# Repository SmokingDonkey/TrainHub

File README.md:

TrainHub
========

This Repo contains hardware and software parts for a automated model railroad:
- TrainTracker: RFID reader platine for train recognition
- ...

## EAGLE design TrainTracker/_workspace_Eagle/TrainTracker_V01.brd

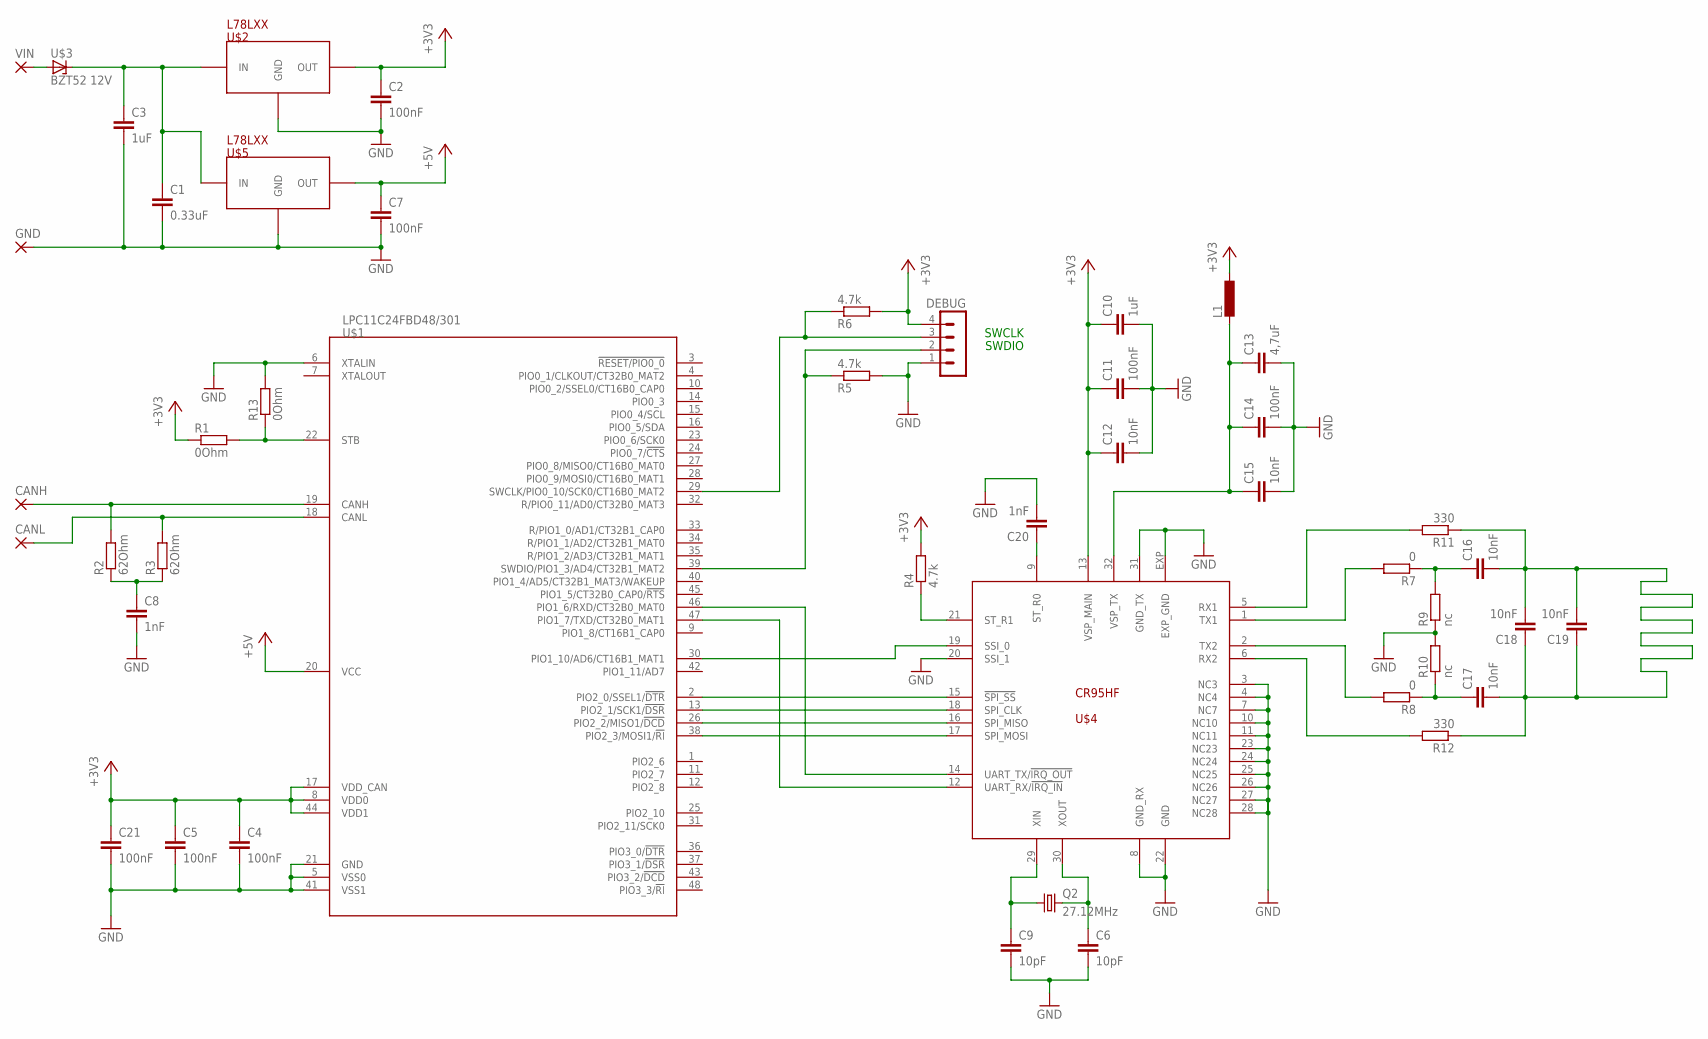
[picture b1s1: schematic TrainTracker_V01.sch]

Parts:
C1: 0.33uF; C0402
C2, C4, C5, C7, C11, C14, C21: 100nF; C0402
C3, C10: 1uF; C0603K
C6, C9: 10pF; C0402
C8, C20: 1nF; C0402
C12, C15, C16, C17, C18, C19: 10nF; C0402
C13: 4,7uF; C0603K
CANH: SMD5; SMD2,54-5,08
CANL: SMD5; SMD2,54-5,08
DEBUG: MA04-1
GND: SMD5; SMD2,54-5,08
L1: L-EUL3216C; L3216C
Q2: 27.12MHz; CTS406
R1, R13: 0Ohm; R0402
R2, R3: 62Ohm; R0402
R4, R5, R6: 4.7k; R0402
R7, R8: 0; R0402
R9, R10: nc; R0402
R11, R12: 330; R0402
U$1: LPC11C24FBD48/301; LQFP48
U$2, U$5: L78LXX; SO8
U$3: BZT52 12V; SOD123
U$4: CR95HF; VFQFPN32
VIN: SMD5; SMD2,54-5,08

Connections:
+3V3: C2.1, C4.1, C5.1, C10.1, C11.1, C12.1, C21.1, DEBUG.4, L1.1, R1.1, R4.2, R6.2, U$1.8 (VDD0), U$1.17 (VDD_CAN), U$1.44 (VDD1), U$2.1 (OUT), U$4.13 (VSP_MAIN)
+5V: C7.1, U$1.20 (VCC), U$5.1 (OUT)
GND: C1.2, C2.2, C3.2, C4.2, C5.2, C6.2, C7.2, C8.2, C9.2, C10.2, C11.2, C12.2, C13.2, C14.2, C15.2, C20.2, C21.2, DEBUG.1, GND.1, R5.2, R9.1, R10.2, R13.2, U$1.5 (VSS0), U$1.6 (XTALIN), U$1.21 (GND), U$1.41 (VSS1), U$2.2 (GND), U$2.3 (GND), U$2.6 (GND), U$2.7 (GND), U$4.3 (NC3), U$4.4 (NC4), U$4.7 (NC7), U$4.8 (GND_RX), U$4.10 (NC10), U$4.11 (NC11), U$4.20 (SSI_1), U$4.22 (GND), U$4.23 (NC23), U$4.24 (NC24), U$4.25 (NC25), U$4.26 (NC26), U$4.27 (NC27), U$4.28 (NC28), U$4.31 (GND_TX), U$4.EXP (EXP_GND), U$5.2 (GND), U$5.3 (GND), U$5.6 (GND), U$5.7 (GND)
unnamed: U$3.1 (A), VIN.1
unnamed: C1.1, C3.1, U$2.8 (IN), U$3.2 (C), U$5.8 (IN)
unnamed: R1.2, R13.1, U$1.22 (STB)
unnamed: C8.1, R2.1, R3.1
unnamed: CANH.1, R2.2, U$1.19 (CANH)
unnamed: CANL.1, R3.2, U$1.18 (CANL)
unnamed: U$1.2 (PIO2_0/SSEL1/!DTR), U$4.15 (!SPI_SS)
unnamed: C20.1, U$4.9 (ST_R0)
unnamed: U$1.13 (PIO2_1/SCK1/!DSR), U$4.18 (SPI_CLK)
unnamed: U$1.26 (PIO2_2/MISO1/!DCD), U$4.16 (SPI_MISO)
unnamed: U$1.38 (PIO2_3/MOSI1/!RI), U$4.17 (SPI_MOSI)
unnamed: R4.1, U$4.21 (ST_R1)
unnamed: U$1.30 (PIO1_10/AD6/CT16B1_MAT1), U$4.19 (SSI_0)
unnamed: U$1.46 (PIO1_6/RXD/CT32B0_MAT0), U$4.14 (UART_TX/!IRQ_OUT)
unnamed: U$1.47 (PIO1_7/TXD/CT32B0_MAT1), U$4.12 (UART_RX/!IRQ_IN)
unnamed: C9.1, Q2.1, U$4.29 (XIN)
unnamed: C6.1, Q2.3 (2), U$4.30 (XOUT)
unnamed: C13.1, C14.1, C15.1, L1.2, U$4.32 (VSP_TX)
unnamed: R11.2, U$4.5 (RX1)
unnamed: R12.2, U$4.6 (RX2)
unnamed: R7.2, U$4.1 (TX1)
unnamed: R8.2, U$4.2 (TX2)
unnamed: C16.1, R7.1, R9.2
unnamed: C17.1, R8.1, R10.1
unnamed: DEBUG.2, R5.1, U$1.39 (SWDIO/PIO1_3/AD4/CT32B1_MAT2)
unnamed: DEBUG.3, R6.1, U$1.29 (SWCLK/PIO0_10/SCK0/CT16B0_MAT2)
unnamed: C16.2, C17.2, C18.1, C18.2, C19.1, C19.2, R11.1, R12.1

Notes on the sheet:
SWDIO
SWCLK

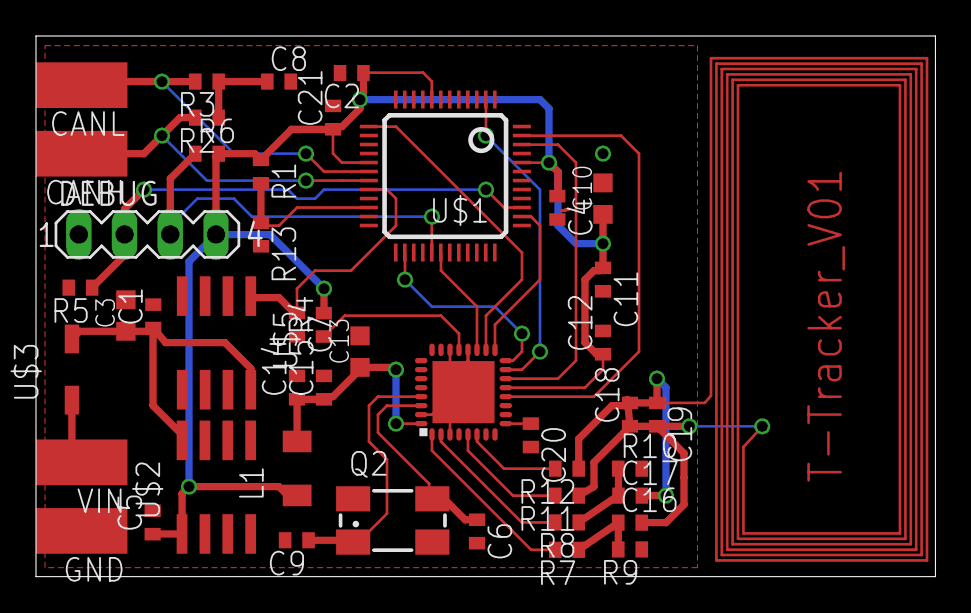
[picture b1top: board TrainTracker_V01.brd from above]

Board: 2 copper layers, 50.0 x 30.0 mm, 46 parts (0 on the bottom side), 30 nets.

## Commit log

2014-04-21 Test commit
    My first commit… :-)
2014-04-21 TrainTracker project added
2014-04-21 clean up
2014-04-23 adding eagle project
2014-04-25 adding lpc11x docu package
2014-04-26 Adding LPC-docu and reorganice repo
2014-06-01 adding documentation
